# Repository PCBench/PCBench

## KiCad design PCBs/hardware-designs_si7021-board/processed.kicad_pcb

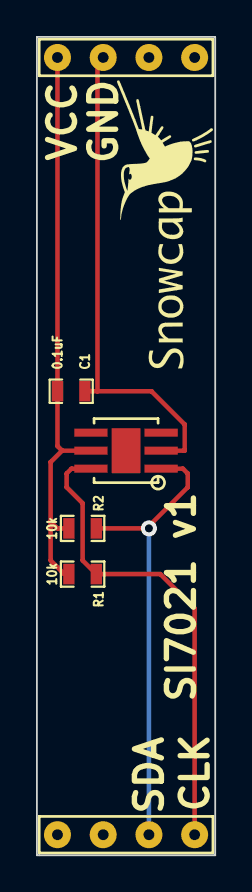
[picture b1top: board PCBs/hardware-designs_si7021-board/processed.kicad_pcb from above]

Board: 2 copper layers, 9.9 x 45.5 mm, 6 parts (0 on the bottom side), 4 nets.

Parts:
C1: 0.1uF; SM0603_Capa
Noname_1: LOGO_SNOWCAP_FRONT
R1, R2: 10k; SM0603_Resistor
U1: SHIELD_I2C
U2: SI7021

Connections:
GND: C1.2, U1.2, U2.2
unnamed: R1.2, U1.8, U2.6
unnamed: R2.2, U1.7, U2.1
VCC: C1.1, R1.1, R2.1, U1.1, U2.5

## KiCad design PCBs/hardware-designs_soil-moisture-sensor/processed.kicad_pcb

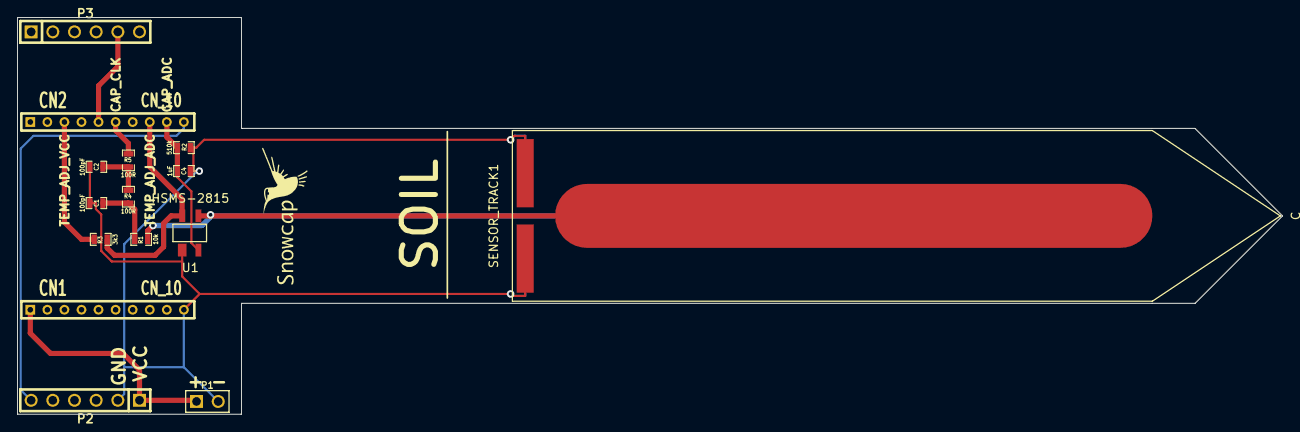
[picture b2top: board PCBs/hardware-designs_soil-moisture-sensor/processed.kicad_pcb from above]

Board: 2 copper layers, 148.2 x 46.5 mm, 16 parts (0 on the bottom side), 11 nets.

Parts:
C1, C2: 100pF; SM0603_Capa
C4: 1uF; SM0603_Capa
CN1, CN2: CN_10; CONN-10-2MM
Noname_1: LOGO_SNOWCAP_FRONT
P1: CONN_2; PIN_ARRAY_2X1
P2, P3: CN_6; PIN_ARRAY-6X1
R1: 10k; SM0603_Resistor
R2: 510k; SM0603_Resistor
R3: 3k3; SM0603_Resistor
R4, R5: 100R; SM0603_Resistor
SENSOR_TRACK1: C; SOIL_SENSOR_CAPACITIVE
U1: HSMS-2815

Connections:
+3.3V: CN1.1, P1.1, P2.1
/CAP_ADC: C4.1, CN2.9, R2.1, U1.2
/CAP_CLK: CN2.6, R5.2
/TEMP_ADJ_ADC: CN2.8, R3.1, U1.3
/TEMP_ADJ_VCC: CN2.3, R3.2
/V_MEASURE1: CN2.10, P2.6
/V_MEASURE2: CN2.5, P3.5
GND: C1.1, C2.1, C4.2, CN1.10, P1.2, P2.2, R2.2, SENSOR_TRACK1.2, U1.1
unnamed: C2.2, R4.2, R5.1
unnamed: C1.2, R1.2, R4.1
unnamed: R1.1, SENSOR_TRACK1.1, U1.4

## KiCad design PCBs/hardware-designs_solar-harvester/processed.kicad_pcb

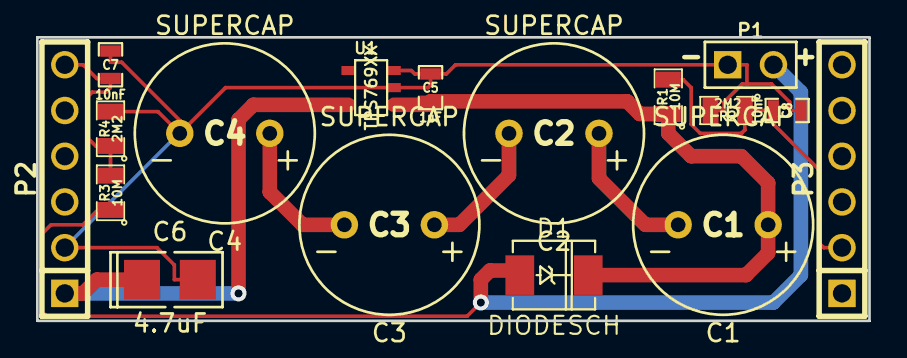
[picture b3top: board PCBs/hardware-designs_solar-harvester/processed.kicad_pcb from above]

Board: 2 copper layers, 46.2 x 15.7 mm, 18 parts (1 on the bottom side), 9 nets.

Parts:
C1, C2, C3, C4: SUPERCAP; SUPERCAP_ESHSR-0010C0-002R7
C5: 1uF; SM0603_Capa
C6: 4.7uF; SM1411_POL
C7, C8: 10nF; SM0603_Capa
D1: DIODESCH; DO-214AC(SMA)
Noname_1: LOGO_SNOWCAP_BACK
P1: CONN_2; PIN_ARRAY_2X1
P2, P3: CONN_6; PIN_ARRAY-6X1
R1, R3: 10M; SM0805
R2, R4: 2M2; SM0805
U1: TPS769XX; SOT23-5

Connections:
/V_MEASURE1: C7.1, P2.6, R3.2, R4.1
/V_MEASURE2: C8.1, P3.2, R1.2, R2.1
GND: C4.2, C5.2, C6.2, C7.2, C8.2, P1.1, P2.2, R2.2, R4.2, U1.2, U1.3
unnamed: C2.2, C3.1
unnamed: D1.1, P1.2, R3.1
unnamed: C6.1, P2.1, U1.5
unnamed: C1.2, C2.1
unnamed: C1.1, C5.1, D1.2, R1.1, U1.1
unnamed: C3.2, C4.1

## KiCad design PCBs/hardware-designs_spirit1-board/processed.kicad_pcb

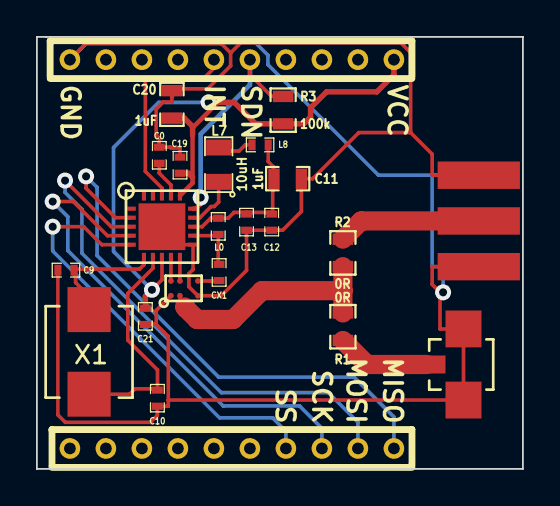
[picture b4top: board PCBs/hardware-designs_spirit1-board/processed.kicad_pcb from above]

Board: 2 copper layers, 27.0 x 24.0 mm, 23 parts (1 on the bottom side), 21 nets.

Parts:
C0, C12: 100nF; SM0402_c
C9: 12pF; SM0402_c
C10: 10pF; SM0402_c
C11, C20: 1uF; SM0603_Capa
C13: 330pF; SM0402_c
C19: 10nF; SM0402_c
C21: 100pF; SM0402_c
CN1: RB-CN10; RB_CN10_2mm
CN2: ANT; RF_SMA
CN3: ANT; U.FL-R-SMT_01
CX1: C; SM0402_c
L0: 150nH; SM0402
L7: 10uH; SM0805
L8: 62nH; SM0402
Noname_1: LOGO_SNOWCAP_BACK
R1, R2: 0R; SM0603_Resistor
R3: 100k; SM0603_Resistor
U1: SPIRIT1; SPIRIT1_QFN20
U2: BALF-SPI-02D3; BALF_SPI_02D3
X1: 50Mhz; CRYSTAL-ABM3-50.000MHZ-D2Y-F-T

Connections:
/50ohm: R1.2, R2.1, U2.B1
GND: C0.2, C9.2, C10.2, C11.2, C12.2, C13.2, C19.2, C20.2, C21.2, CN1.10, CN2.2, CN3.2, U1.11, U1.21, U2.A1, U2.C1
unnamed: CN1.11, U1.2
unnamed: CN1.12, U1.3
unnamed: CN1.13, U1.4
unnamed: CN1.14, U1.5
unnamed: C0.1, U1.17
unnamed: CN1.5, R3.2, U1.15
unnamed: CN1.6, U1.18
unnamed: CN3.1, R1.1
unnamed: CN2.1, R2.2
unnamed: C11.1, C12.1, C13.1, L0.2, L8.2, U1.13
unnamed: L7.2, L8.1
unnamed: C9.1, U1.6, X1.1
unnamed: C10.1, U1.7, X1.2
unnamed: L7.1, U1.14
unnamed: U1.9, U2.A2
unnamed: U1.10, U2.B2
unnamed: CX1.1, L0.1, U1.12
unnamed: CX1.2, U2.C2
VCC: C19.1, C20.1, C21.1, CN1.1, R3.1, U1.8, U1.16

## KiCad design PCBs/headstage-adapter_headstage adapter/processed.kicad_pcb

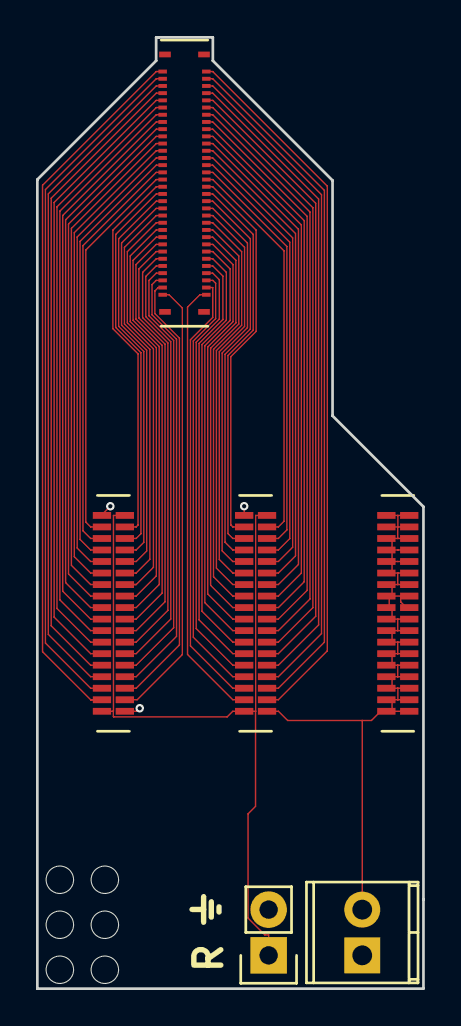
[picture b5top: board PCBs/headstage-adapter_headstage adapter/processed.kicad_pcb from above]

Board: 4 copper layers, 21.4 x 52.8 mm, 12 parts (0 on the bottom side), 66 nets.

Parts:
JP1: Jumper_NO_Small; Socket_Strip_Straight_1x02
M1, M2, M3, M4, M5, M6: #0 drill hole; #0_drill_hole
P1: 502426-6410; Molex_SlimStack_receptacle_64_0.4mm_pitch
P2: 1725656; TerminalBlock_Pheonix_MPT-2.54mm_2pol
U1, U2, U3: A79026-001; omnetics_connector_36_pin

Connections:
/1: P1.63, U1.3
/2: P1.1, U1.4
/3: P1.61, U1.5
/4: P1.3, U1.6
/5: P1.59, U1.7
/6: P1.5, U1.8
/7: P1.57, U1.9
/8: P1.7, U1.10
/9: P1.55, U1.11
/10: P1.9, U1.12
/11: P1.53, U1.13
/12: P1.11, U1.14
/13: P1.51, U1.15
/14: P1.13, U1.16
/15: P1.49, U1.17
/16: P1.15, U1.18
/17: P1.47, U1.19
/18: P1.17, U1.20
/19: P1.45, U1.21
/20: P1.19, U1.22
/21: P1.43, U1.23
/22: P1.21, U1.24
/23: P1.41, U1.25
/24: P1.23, U1.26
/25: P1.39, U1.27
/26: P1.25, U1.28
/27: P1.37, U1.29
/28: P1.27, U1.30
/29: P1.35, U1.31
/30: P1.29, U1.32
/31: P1.33, U1.33
/32: P1.31, U1.34
/33: P1.2, U2.3
/34: P1.64, U2.4
/35: P1.4, U2.5
/36: P1.62, U2.6
/37: P1.6, U2.7
/38: P1.60, U2.8
/39: P1.8, U2.9
/40: P1.58, U2.10
/41: P1.10, U2.11
/42: P1.56, U2.12
/43: P1.12, U2.13
/44: P1.54, U2.14
/45: P1.14, U2.15
/46: P1.52, U2.16
/47: P1.16, U2.17
/48: P1.50, U2.18
/49: P1.18, U2.19
/50: P1.48, U2.20
/51: P1.20, U2.21
/52: P1.46, U2.22
/53: P1.22, U2.23
/54: P1.44, U2.24
/55: P1.24, U2.25
/56: P1.42, U2.26
/57: P1.26, U2.27
/58: P1.40, U2.28
/59: P1.28, U2.29
/60: P1.38, U2.30
/61: P1.30, U2.31
/62: P1.36, U2.32
/63: P1.32, U2.33
/64: P1.34, U2.34
/G: JP1.2, P2.2, U1.1, U1.36, U2.1, U2.36, U3.1, U3.2, U3.3, U3.4, U3.5, U3.6, U3.7, U3.8, U3.9, U3.10, U3.11, U3.12, U3.13, U3.14, U3.15, U3.16, U3.17, U3.18, U3.19, U3.20, U3.21, U3.22, U3.23, U3.24, U3.25, U3.26, U3.27, U3.28, U3.29, U3.30, U3.31, U3.32, U3.33, U3.34, U3.35, U3.36
/R: JP1.1, P2.1, U1.2, U1.35, U2.2, U2.35

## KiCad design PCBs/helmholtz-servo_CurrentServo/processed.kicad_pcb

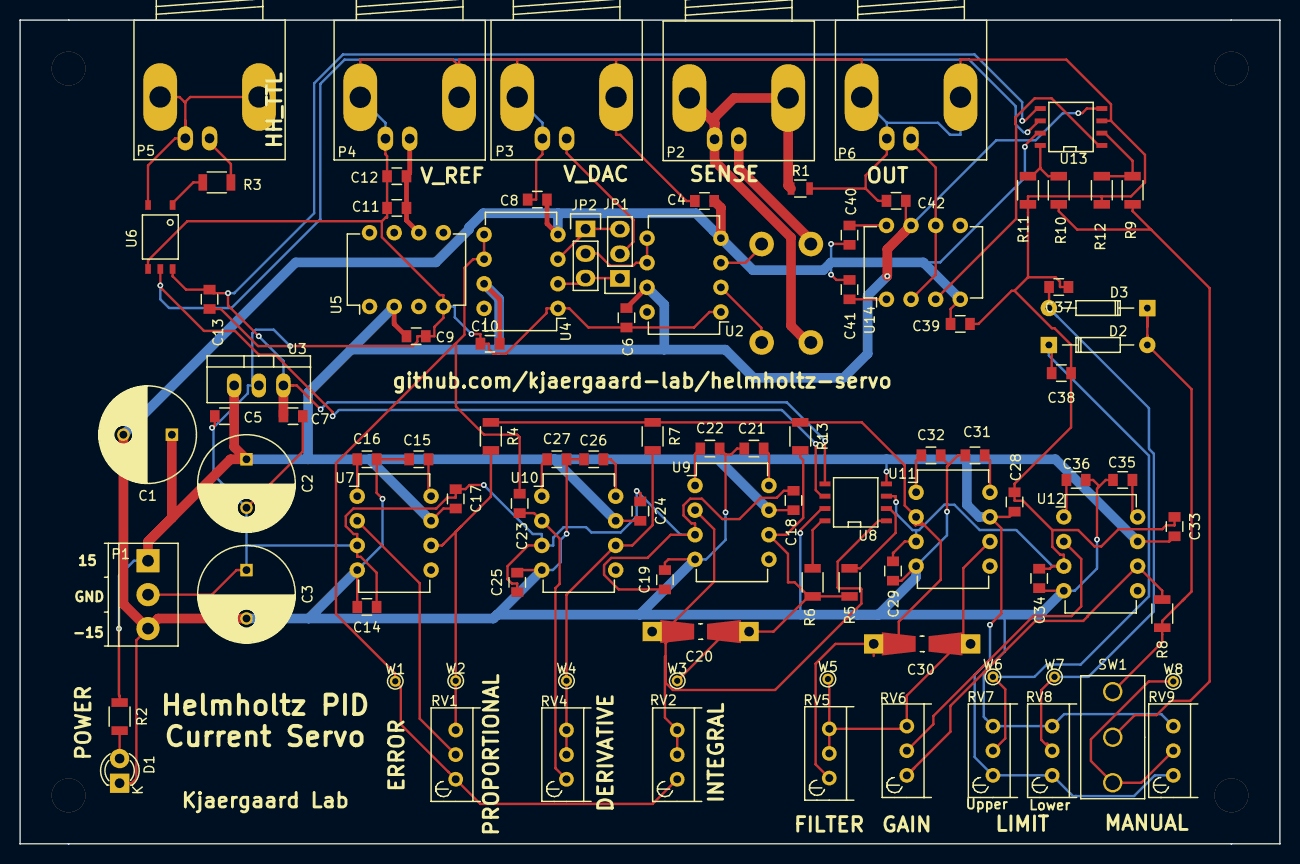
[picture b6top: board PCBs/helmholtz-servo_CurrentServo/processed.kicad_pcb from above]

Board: 2 copper layers, 130.0 x 85.0 mm, 97 parts (1 on the bottom side), 52 nets.

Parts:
C1: 22u; C_Radial_D10_L13_P5
C2, C3: 100u; C_Radial_D10_L16_P5
C4, C6, C8, C10, C12, C13, C14, C15, C16, C17, C18, C19, C21, C22, C23, C24, C25, C26, C27, C28, C29, C31, C32, C33, C34, C35, C36, C37, C38, C39, C40, C41, C42: 100n; C_0805
C5: 330n; C_0805
C7: 10n; C_0805
C9, C11: 2.2u; C_0805
C20, C30: 100n; Resistor_SMD+THTuniversal_0805to1206_RM10_HandSoldering
D1: LED; LED-3MM
D2, D3: D; Diode_DO-35_SOD27_Horizontal_RM10
JP1, JP2: JUMPER3; Pin_Header_Straight_1x03
P1: POWER; TerminalBlock_Pheonix_PT-3.5mm_3pol
P2: SENSE; BNC_Socket_TYCO-AMP_LargePads
P3: V_DAC; BNC_Socket_TYCO-AMP_LargePads
P4: VREF; BNC_Socket_TYCO-AMP_LargePads
P5: HH_IN; BNC_Socket_TYCO-AMP_LargePads
P6: OUT; BNC_Socket_TYCO-AMP_LargePads
R1: 0R; R_0805
R2: 1K2; R_1206
R3: 330; R_1206
R4, R7, R13: 10K; R_1206
R5, R10, R12: DNP; R_1206
R6: 3K3; R_1206
R8: 51K; R_1206
R9, R11: 50; R_1206
RV1, RV2, RV4, RV5, RV9: 10K; Potentiometer_Bourns_3296W_3-8Zoll_Inline_ScrewUp
RV6: 100K; Potentiometer_Bourns_3296W_3-8Zoll_Inline_ScrewUp
RV7, RV8: 2K; Potentiometer_Bourns_3296W_3-8Zoll_Inline_ScrewUp
SW1: 1AS2T2B4M2RE; Switch_SPDT_4.7mm
U1: VHP4Z
U2, U4: INA105; DIP-8_W7.62mm
U3: 78L05; TO-220_Neutral123_Vertical
U5: MAX6350; DIP-8_W7.62mm
U6: TLP116A
U7, U9, U10, U11, U12, U14: TC7650; DIP-8_W7.62mm
U8, U13: DG419; SOIC-8-N
W1: ERROR; PINTST
W2: PROP; PINTST
W3: INT; PINTST
W4: DERIV; PINTST
W5: FILTER; PINTST
W6: ULIM; PINTST
W7: LLIM; PINTST
W8: MANUAL; PINTST

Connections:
/OutputConditioning/CTRL_IN: C30.2, R4.1, R7.1, R13.1, RV5.1, U11.2
/OutputConditioning/LLIMIT: C37.2, D3.2, RV8.2, W7.1
/OutputConditioning/SIG_OUT: P6.1, U14.2, U14.6
/OutputConditioning/ULIMIT: C38.2, D2.1, RV7.2, W6.1
/PIDAmps/ERROR: C23.2, RV1.1, RV2.1, U4.5, U4.6, W1.1
GND: C2.2, C3.1, C4.2, C5.2, C6.1, C7.2, C8.1, C9.2, C10.1, C11.2, C12.2, C13.2, C14.1, C17.1, C18.1, C19.1, C24.1, C25.1, C28.1, C29.1, C33.1, C34.1, C37.1, C38.1, C39.2, C42.1, P1.2, P3.2, P4.2, P6.2, R1.2, R11.2, R12.2, U2.1, U3.2, U4.1, U5.4, U6.4, U7.3, U8.3, U9.3, U10.3, U11.3, U12.3, U13.3
HH_TTL: U6.5, U8.6, U13.6
unnamed: C11.1, C12.1, P4.1, U5.6
unnamed: C15.1, U7.8
unnamed: C16.1, U7.1
unnamed: C20.1, R5.1, R6.1, R13.2, U9.6, W3.1
unnamed: C20.2, RV2.2, RV2.3, U8.1, U9.2
unnamed: C21.1, U9.8
unnamed: C22.1, U9.1
unnamed: C23.1, RV4.1, U10.2
unnamed: C26.1, U10.8
unnamed: C27.1, U10.1
unnamed: C30.1, RV5.2, RV5.3, RV6.3, U11.6, W5.1
unnamed: C31.1, U11.8
unnamed: C32.1, U11.1
unnamed: C35.1, U12.8
unnamed: C36.1, U12.1
unnamed: C40.1, U14.8
unnamed: C41.1, U14.1
unnamed: D1.2, R2.2
unnamed: D2.2, D3.1, R8.1, SW1.1
unnamed: JP1.1, JP2.3, U4.2
unnamed: JP1.2, P3.1
unnamed: JP1.3, JP2.1, U4.3
unnamed: JP2.2, U2.5, U2.6
unnamed: P2.1, U1.1
unnamed: P2.2, R1.1, U1.2
unnamed: P5.1, R3.2
unnamed: P5.2, U6.3
unnamed: R3.1, U6.1
unnamed: R4.2, RV1.3, U7.6, W2.1
unnamed: R5.2, U8.2
unnamed: R6.2, U8.8
unnamed: R7.2, RV4.2, RV4.3, U10.6, W4.1
unnamed: R8.2, RV6.1, U12.6
unnamed: R10.1, R11.1, U13.8
unnamed: R9.2, R10.2, SW1.2
unnamed: R9.1, R12.1, U13.2
unnamed: RV1.2, U7.2
unnamed: RV6.2, U12.2
unnamed: RV9.2, SW1.3, W8.1
unnamed: U1.3, U2.3
unnamed: U1.4, U2.2
unnamed: U13.1, U14.3
VCC: C7.1, C13.1, U3.3, U6.6, U8.5, U13.5
VDD: C1.1, C2.1, C5.1, C6.2, C9.1, C10.2, C17.2, C18.2, C24.2, C28.2, C33.2, C42.2, P1.1, R2.1, RV7.1, RV8.1, RV9.1, U2.7, U3.1, U4.7, U5.2, U7.7, U8.4, U9.7, U10.7, U11.7, U12.7, U13.4, U14.7
VSS: C1.2, C3.2, C4.1, C8.2, C14.2, C15.2, C16.2, C19.2, C21.2, C22.2, C25.2, C26.2, C27.2, C29.2, C31.2, C32.2, C34.2, C35.2, C36.2, C39.1, C40.2, C41.2, D1.1, P1.3, RV7.3, RV8.3, RV9.3, U2.4, U4.4, U7.4, U8.7, U9.4, U10.4, U11.4, U12.4, U13.7, U14.4

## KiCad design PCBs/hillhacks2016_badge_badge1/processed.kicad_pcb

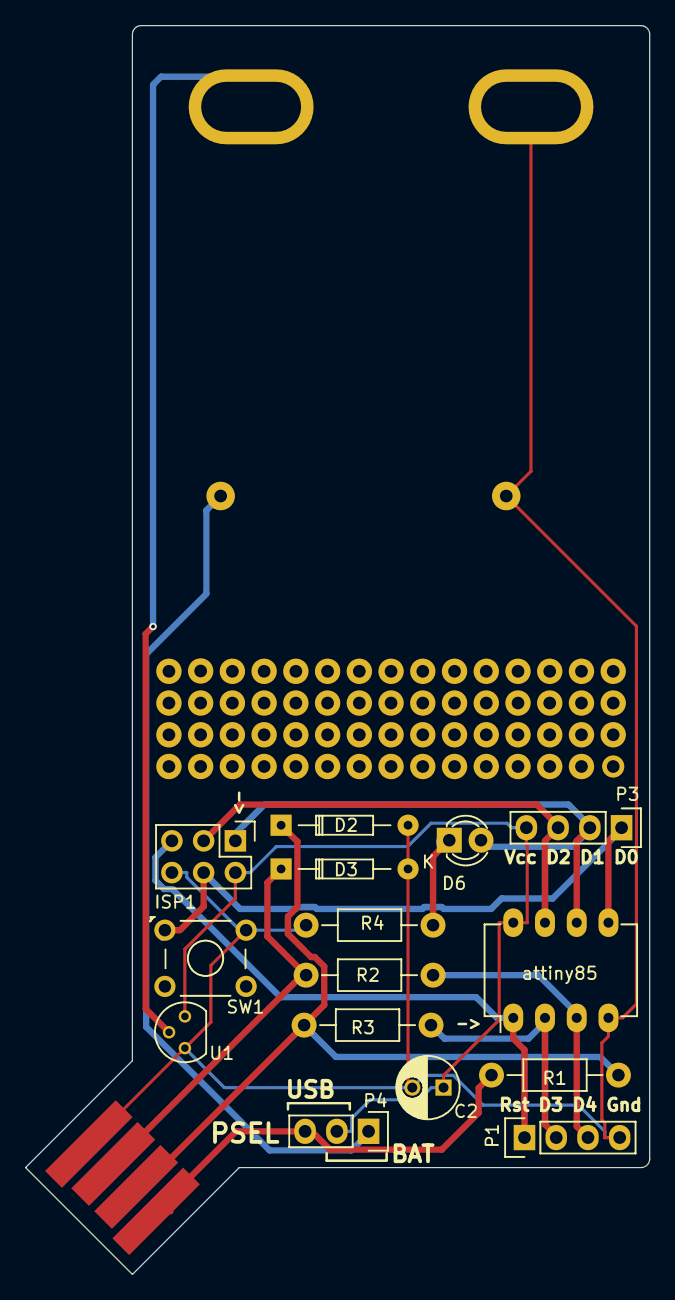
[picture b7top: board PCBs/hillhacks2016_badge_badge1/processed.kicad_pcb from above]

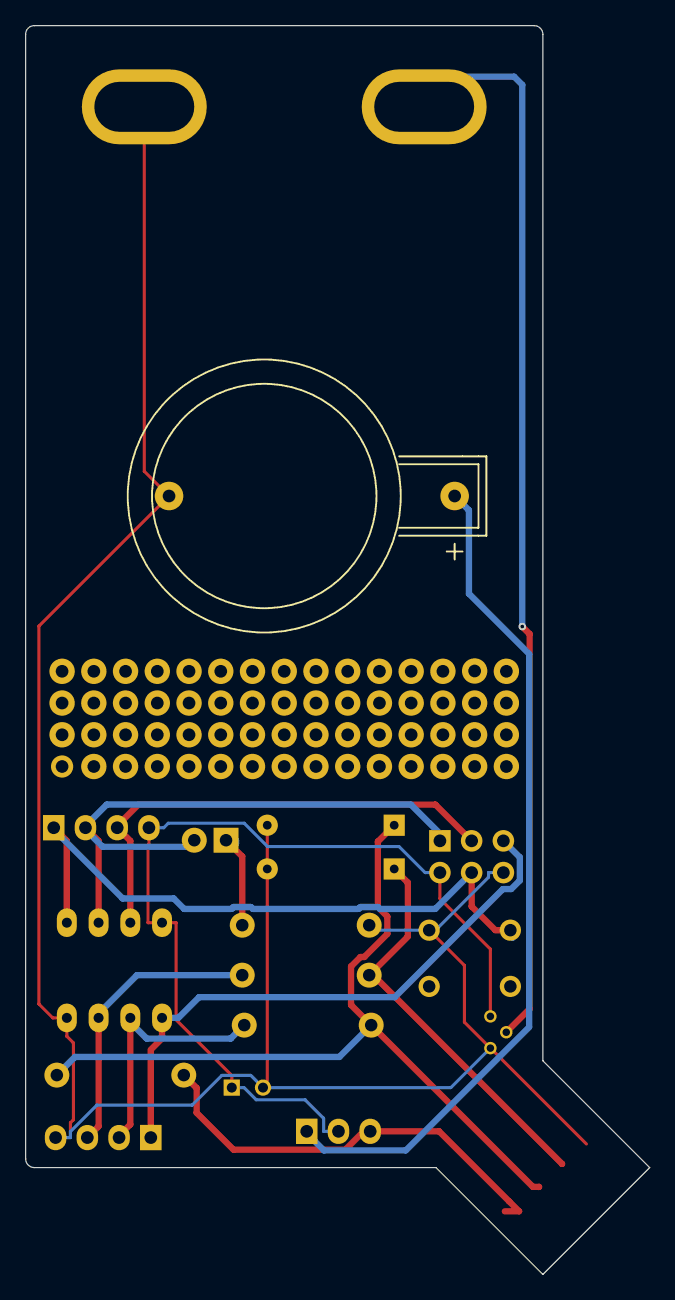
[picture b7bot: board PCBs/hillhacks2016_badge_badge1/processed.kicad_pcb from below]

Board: 2 copper layers, 50.0 x 100.0 mm, 22 parts (2 on the bottom side), 14 nets.

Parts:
BT1: Battery; CR2032H
C2: 4.7uF; C_Radial_D5_L11_P2.5
D2, D3: 3.6V BZX79C3V6; Diode_DO-35_SOD27_Horizontal_RM10
D6: LED; LED-3MM
ISP1: AVR-ISP-6; Pin_Header_Straight_2x03
P1, P3: CONN_01X04; Pin_Header_Straight_1x04
P2: USB_A; usb-PCB
P4: CONN_01X03; Pin_Header_Straight_1x03
R1: 1.5k; Resistor_Horizontal_RM10mm
R2, R3: 68; Resistor_Horizontal_RM10mm
R4: 470; Resistor_Horizontal_RM10mm
SW1: SW_PUSH; OPL_DIP_BUTTON_TS-1109_BEST_SHENZEN
U1: MCP1700-3302E/TO; TO-92_Molded_Narrow
U4: proto_area
U5, U6: badge_hole2; badge_hole_6mmx3mm(+2mmCu)
U7, U8: custom_logo; tesseract
attiny85: ATTINY85-S; DIP-8_W7.62mm_LongPads

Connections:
/D0: ISP1.4, P3.1, SW1.1, attiny85.5
/D1: D6.2, ISP1.1, P3.2, attiny85.6
/D2: ISP1.3, P3.3, attiny85.7
/D3: P1.2, R3.2, attiny85.2
/D4: P1.3, R2.2, attiny85.3
/RST: ISP1.5, P1.1, attiny85.1
/USB-D+: D3.1, P2.3, R2.1
/USB-D-: D2.1, P2.2, R1.1, R3.1
/VBAT: BT1.1, P4.1
/VBUS: P2.1, P4.3, R1.2
/V_sec_bat: U1.2, U5.1
GND: BT1.2, C2.2, D2.2, D3.2, ISP1.6, P1.4, P2.4, R4.2, SW1.2, U1.1, U6.1, attiny85.4
unnamed: D6.1, R4.1
VCC: C2.1, ISP1.2, P3.4, P4.2, U1.3, attiny85.8
